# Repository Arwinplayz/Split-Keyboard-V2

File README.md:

# Split-Keyboard V2

I recently got my PCB from JLCPCB but I realised that I had accidentally inverted the holes for the hotswap sockets. This makes it physically impossible for me to actually assembly it properly. Learning from my failures, I decided to make a V2 which would not only fix the socket problem but also allow me to redo/refine some features. That is I want to add a LiPo battery and change the requirement of having both sides plugged in separately to the PC. I already have the parts to build the keyboard so the grant is only for the PCB (and possibly extra stuff such as LiPo battery, resistors, JST PH connectors, etc)

## Planning

I recently got my PCB from JLCPCB but I realised that I had accidentally inverted the holes for the hotswap sockets. This makes it physically impossible for me to actually assembly it properly. (Awkward placement + overlap with other components)

Learning from my failures, I decided to make a V2 which would not only fix the socket problem but also allow me to redo/refine some features. That is I want to add a LiPo battery and change the requirement of having both sides plugged in separately to the PC. I already have the parts to build the keyboard so the grant is only for the PCB (and possibly extra stuff such as LiPo battery, resistors, JST PH connectors, etc)

GOALS:

Fix hotswap socket orientation
Added better connectivity between the split keyboards (Master and Slave RP2040)
Add support for 1s 3.4V LiPo Battery

## Heavily Modified Schematic

So firstly, I realised that to use the master and slave approach, I needed a TRRS which connects the halves via UART. This meant that I needed a UARTTX, UARTRX but all my gpio pins were occupied. After some research I found that the nice!nano v2 was a good choice as it had the same Nordic chip. This allowed for bluetooth connection, a built in linear Li-Po charging circuit which helps avoid clutter. Furthermore, I added a 2 pin JST-PH connector for the Li-Po battery. There is also an RGB LED which will signal green for charged, yellow for 50$, red for low and blue for charging.

## Routed half the PCB

So I managed to route half the PCB now. There were many problems related to footprints as the Nice!Nano doesn't really have a goof publicly available one and so I had to design it myself. Also I added LED lights for every switch and ensured the hotswap sockets were orientated the right way.

## Finished Routing the PCB

So it took me a while to figure out how to mirror the left side. There was no easy way to do so I ended up flipping the edgecut and then redoing all the wiring. There is only 1 error on the ERC which is the left and right side aren't connected by this will get fixed with a TRRC cable.

## Gerber Files

I decided to get PCBA due to the keybaord requiring several LED and Diodes which all require a certain orientation to work properly. A few components require PCBA to be placed. I do have 1 or 2 components which I will hand solder myself to help reduce the costs. The PCB was too large for PCBA so I have to order each half of the PCB seperately.

## BOM

So since I already have most of the components such as rotary encoder, key switches, keycaps, etc, the BOM is prely for the parts I need for the PCB (the extra stuff that I didn't solder from JLC). So the total comes to about 227.98 USD. I really do not know how to make it cheaper as I've sourced everything from the cheapest sites I could find i.e aliexpress.

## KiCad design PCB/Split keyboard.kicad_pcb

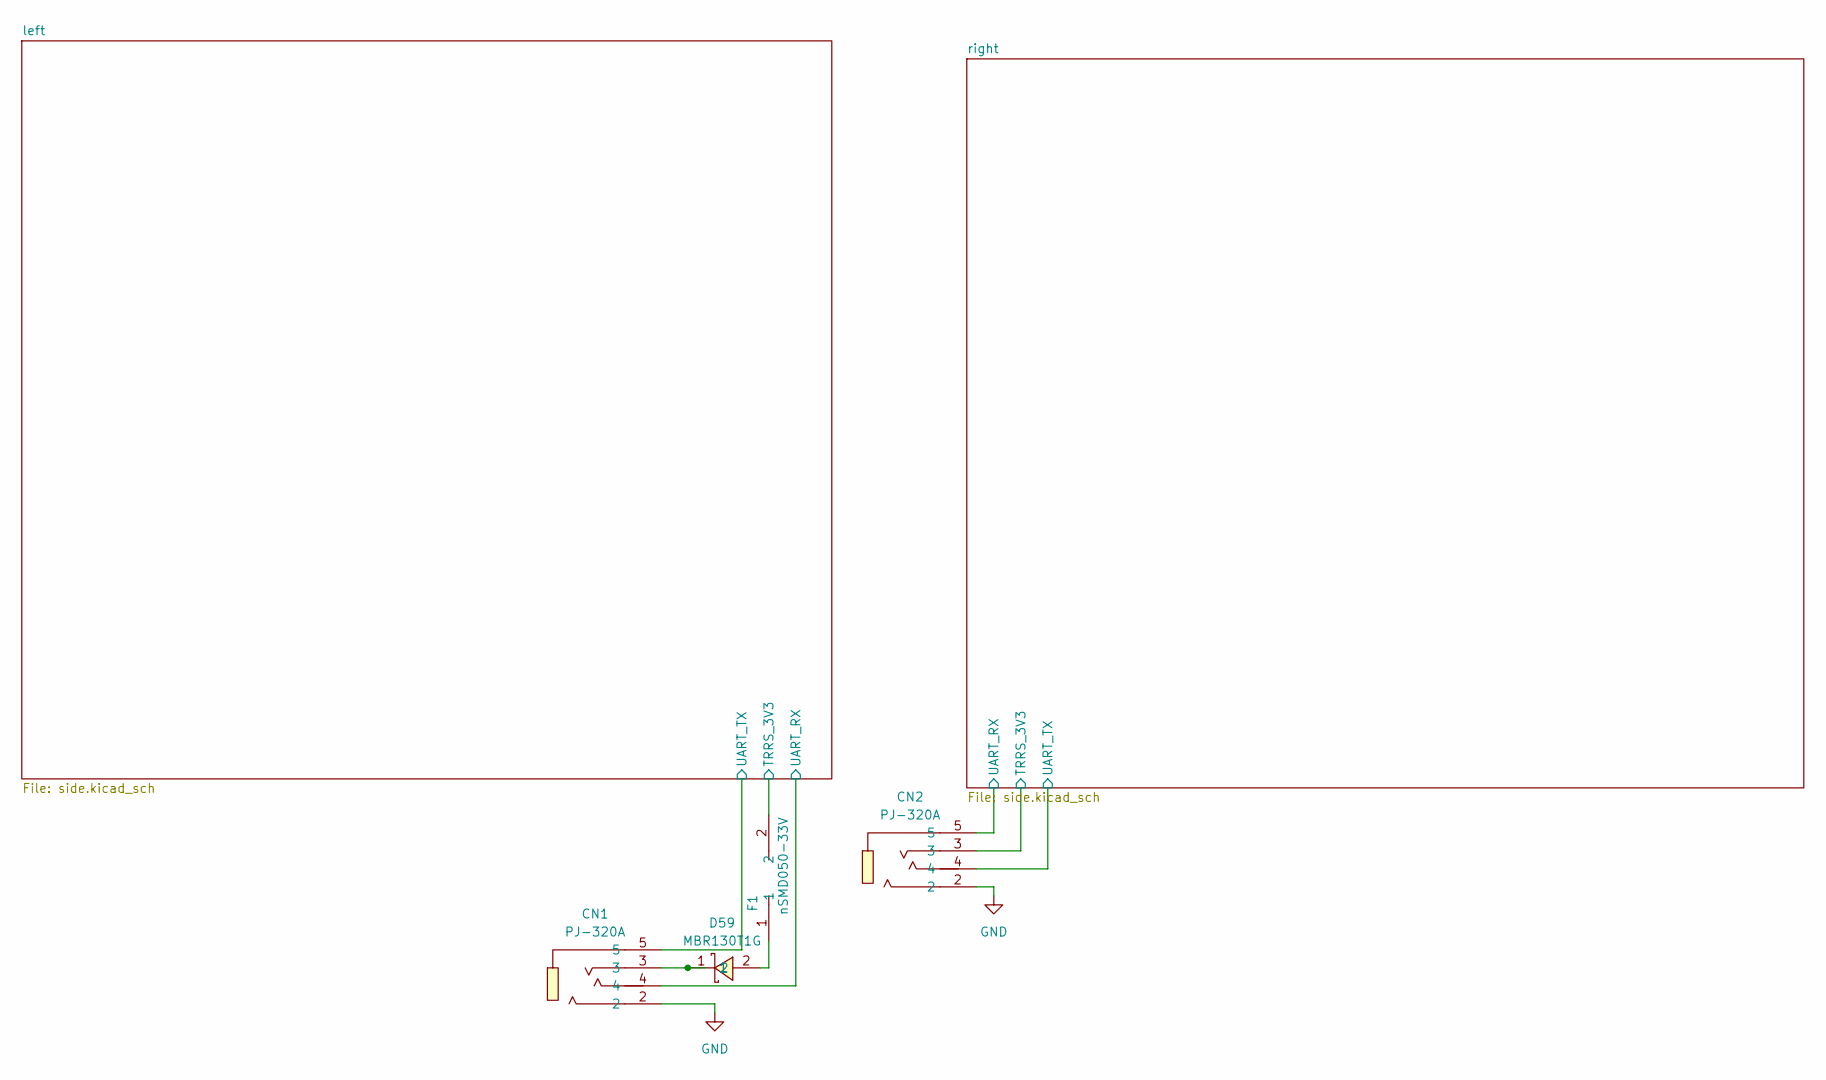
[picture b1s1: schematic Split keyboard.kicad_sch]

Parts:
CN1, CN2: PJ-320A; AUDIO-TH_XKB_PJ-320A; LCSC Part C2884926
D59: MBR130T1G; SOD-123_L2.8-W1.8-LS3.7-RD; LCSC Part C82461
F1: nSMD050-33V; F1206; LCSC Part C70077

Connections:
/left/UART_RX: CN1.4; also elsewhere on the board
/left/UART_TX: CN1.5; also elsewhere on the board
/left/VCC: F1.2; also elsewhere on the board
/right/UART_RX: CN2.5; also elsewhere on the board
/right/UART_TX: CN2.4; also elsewhere on the board
/right/VCC: CN2.3; also elsewhere on the board
GND: CN1.2, CN2.2; also elsewhere on the board
unnamed: CN1.3, D59.1
unnamed: D59.2, F1.1

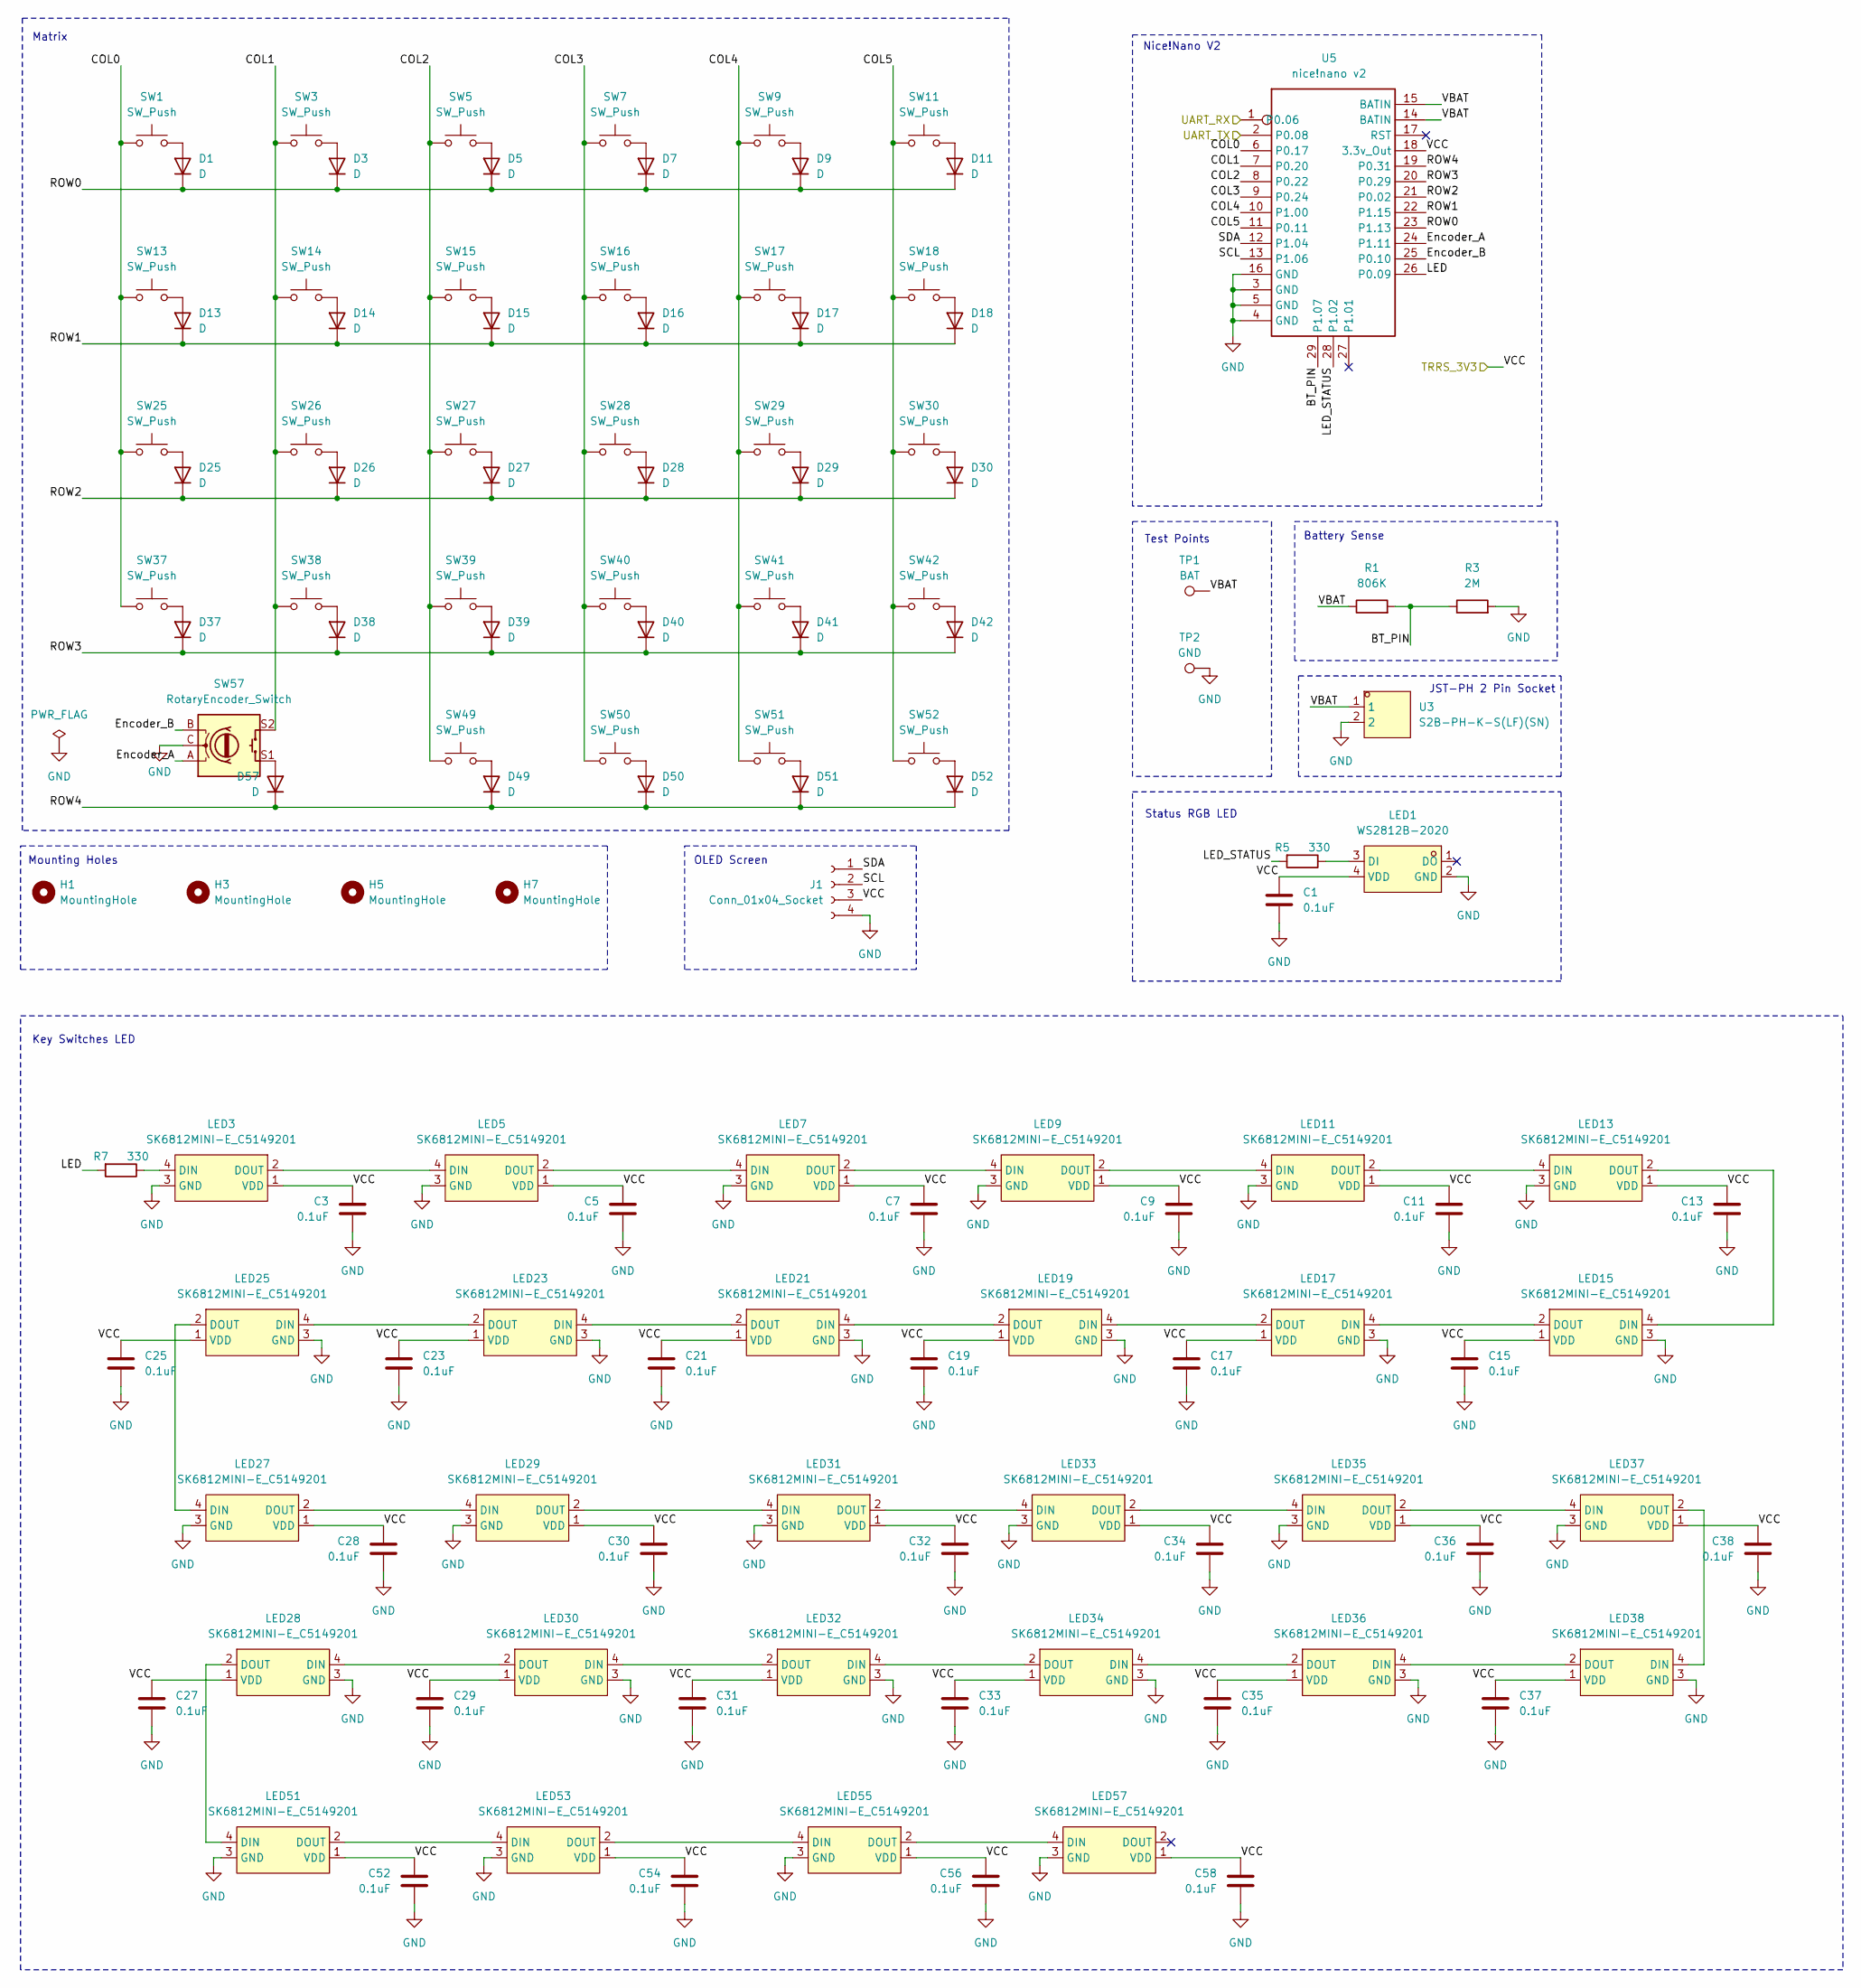
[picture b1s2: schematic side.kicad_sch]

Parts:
C1, C3, C5, C7, C9, C11, C13, C15, C17, C19, C21, C23, C25, C27, C28, C29, C30, C31, C32, C33, C34, C35, C36, C37, C38, C52, C54, C56, C58: 0.1uF; C_0603_1608Metric
D1, D3, D5, D7, D9, D11, D13, D14, D15, D16, D17, D18, D25, D26, D27, D28, D29, D30, D37, D38, D39, D40, D41, D42, D49, D50, D51, D52, D57: D; D_SOD-123
H1, H3, H5, H7: MountingHole; MountingHole_3.2mm_M3
J1: Conn_01x04_Socket; PinSocket_1x04_P2.54mm_Vertical
LED1: WS2812B-2020; LED-SMD_4P-L2.0-W2.0-TL_WS2812B-2020; LCSC Part C965555
LED3, LED5, LED7, LED9, LED11, LED13, LED15, LED17, LED19, LED21, LED23, LED25, LED27, LED28, LED29, LED30, LED31, LED32, LED33, LED34, LED35, LED36, LED37, LED38, LED51, LED53, LED55, LED57: SK6812MINI-E_C5149201; LED-SMD_L3.2-W2.8-LS5.9_SK6812MINI-E; LCSC Part C5149201
R1: 806K; R_0805_2012Metric
R3: 2M; R_0805_2012Metric
R5, R7: 330; R_0603_1608Metric
SW1, SW3, SW5, SW7, SW9, SW11, SW13, SW14, SW15, SW16, SW17, SW18, SW25, SW26, SW27, SW28, SW29, SW30, SW37, SW38, SW39, SW40, SW41, SW42, SW49, SW50, SW51, SW52: SW_Push; SW_choc_v1_HS_CPG135001S30_1u
SW57: RotaryEncoder_Switch; RotaryEncoder_Alps_EC11E-Switch_Vertical_H20mm
TP1: BAT; TestPoint_Pad_D2.0mm
TP2: GND; TestPoint_Pad_D2.0mm
U3: S2B-PH-K-S(LF)(SN); CONN-TH_S2B-PH-K-S-LF-SN; LCSC Part C173752
U5: nice!nano v2; NICE!NANO V2_2

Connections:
/left/BT_PIN: R1.2, R3.1, U5.29 (P1.07)
/left/COL0: SW1.1, SW13.1, SW25.1, SW37.1, U5.6 (P0.17)
/left/COL1: SW3.1, SW14.1, SW26.1, SW38.1, SW57.S2, U5.7 (P0.20)
/left/COL2: SW5.1, SW15.1, SW27.1, SW39.1, SW49.1, U5.8 (P0.22)
/left/COL3: SW7.1, SW16.1, SW28.1, SW40.1, SW50.1, U5.9 (P0.24)
/left/COL4: SW9.1, SW17.1, SW29.1, SW41.1, SW51.1, U5.10 (P1.00)
/left/COL5: SW11.1, SW18.1, SW30.1, SW42.1, SW52.1, U5.11 (P0.11)
/left/Encoder_A: SW57.A, U5.24 (P1.11)
/left/Encoder_B: SW57.B, U5.25 (P0.10)
/left/LED: R7.2, U5.26 (P0.09)
/left/LED_STATUS: R5.2, U5.28 (P1.02)
/left/ROW0: D1.1 (K), D3.1 (K), D5.1 (K), D7.1 (K), D9.1 (K), D11.1 (K), U5.23 (P1.13)
/left/ROW1: D13.1 (K), D14.1 (K), D15.1 (K), D16.1 (K), D17.1 (K), D18.1 (K), U5.22 (P1.15)
/left/ROW2: D25.1 (K), D26.1 (K), D27.1 (K), D28.1 (K), D29.1 (K), D30.1 (K), U5.21 (P0.02)
/left/ROW3: D37.1 (K), D38.1 (K), D39.1 (K), D40.1 (K), D41.1 (K), D42.1 (K), U5.20 (P0.29)
/left/ROW4: D49.1 (K), D50.1 (K), D51.1 (K), D52.1 (K), D57.1 (K), U5.19 (P0.31)
/left/SCL: J1.2, U5.13 (P1.06)
/left/SDA: J1.1, U5.12 (P1.04)
/left/UART_RX: U5.1 (P0.06); also elsewhere on the board
/left/UART_TX: U5.2 (P0.08); also elsewhere on the board
/left/VBAT: R1.1, TP1.1, U3.1, U5.14 (BATIN), U5.15 (BATIN)
/left/VCC: C1.1, C3.1, C5.1, C7.1, C9.1, C11.1, C13.1, C15.1, C17.1, C19.1, C21.1, C23.1, C25.1, C27.1, C28.1, C29.1, C30.1, C31.1, C32.1, C33.1, C34.1, C35.1, C36.1, C37.1, C38.1, C52.1, C54.1, C56.1, C58.1, J1.3, LED1.4 (VDD), LED3.1 (VDD), LED5.1 (VDD), LED7.1 (VDD), LED9.1 (VDD), LED11.1 (VDD), LED13.1 (VDD), LED15.1 (VDD), LED17.1 (VDD), LED19.1 (VDD), LED21.1 (VDD), LED23.1 (VDD), LED25.1 (VDD), LED27.1 (VDD), LED28.1 (VDD), LED29.1 (VDD), LED30.1 (VDD), LED31.1 (VDD), LED32.1 (VDD), LED33.1 (VDD), LED34.1 (VDD), LED35.1 (VDD), LED36.1 (VDD), LED37.1 (VDD), LED38.1 (VDD), LED51.1 (VDD), LED53.1 (VDD), LED55.1 (VDD), LED57.1 (VDD), U5.18 (3.3v_Out); also elsewhere on the board
GND: C1.2, C3.2, C5.2, C7.2, C9.2, C11.2, C13.2, C15.2, C17.2, C19.2, C21.2, C23.2, C25.2, C27.2, C28.2, C29.2, C30.2, C31.2, C32.2, C33.2, C34.2, C35.2, C36.2, C37.2, C38.2, C52.2, C54.2, C56.2, C58.2, J1.4, LED1.2 (GND), LED3.3 (GND), LED5.3 (GND), LED7.3 (GND), LED9.3 (GND), LED11.3 (GND), LED13.3 (GND), LED15.3 (GND), LED17.3 (GND), LED19.3 (GND), LED21.3 (GND), LED23.3 (GND), LED25.3 (GND), LED27.3 (GND), LED28.3 (GND), LED29.3 (GND), LED30.3 (GND), LED31.3 (GND), LED32.3 (GND), LED33.3 (GND), LED34.3 (GND), LED35.3 (GND), LED36.3 (GND), LED37.3 (GND), LED38.3 (GND), LED51.3 (GND), LED53.3 (GND), LED55.3 (GND), LED57.3 (GND), R3.2, SW57.C, TP2.1, U3.2, U5.3 (GND), U5.4 (GND), U5.5 (GND), U5.16 (GND); also elsewhere on the board
unnamed: D1.2 (A), SW1.2
unnamed: D3.2 (A), SW3.2
unnamed: D5.2 (A), SW5.2
unnamed: D7.2 (A), SW7.2
unnamed: D9.2 (A), SW9.2
unnamed: D11.2 (A), SW11.2
unnamed: D13.2 (A), SW13.2
unnamed: D14.2 (A), SW14.2
unnamed: D15.2 (A), SW15.2
unnamed: D16.2 (A), SW16.2
unnamed: D17.2 (A), SW17.2
unnamed: D18.2 (A), SW18.2
unnamed: D25.2 (A), SW25.2
unnamed: D26.2 (A), SW26.2
unnamed: D27.2 (A), SW27.2
unnamed: D28.2 (A), SW28.2
unnamed: D29.2 (A), SW29.2
unnamed: D30.2 (A), SW30.2
unnamed: D37.2 (A), SW37.2
unnamed: D38.2 (A), SW38.2
unnamed: D39.2 (A), SW39.2
unnamed: D40.2 (A), SW40.2
unnamed: D41.2 (A), SW41.2
unnamed: D42.2 (A), SW42.2
unnamed: D49.2 (A), SW49.2
unnamed: D50.2 (A), SW50.2
unnamed: D51.2 (A), SW51.2
unnamed: D52.2 (A), SW52.2
unnamed: D57.2 (A), SW57.S1
unnamed: LED1.3 (DI), R5.1
unnamed: LED3.4 (DIN), R7.1
unnamed: LED3.2 (DOUT), LED5.4 (DIN)
unnamed: LED5.2 (DOUT), LED7.4 (DIN)
unnamed: LED7.2 (DOUT), LED9.4 (DIN)
unnamed: LED9.2 (DOUT), LED11.4 (DIN)
unnamed: LED11.2 (DOUT), LED13.4 (DIN)
unnamed: LED13.2 (DOUT), LED15.4 (DIN)
unnamed: LED15.2 (DOUT), LED17.4 (DIN)
unnamed: LED17.2 (DOUT), LED19.4 (DIN)
unnamed: LED19.2 (DOUT), LED21.4 (DIN)
unnamed: LED21.2 (DOUT), LED23.4 (DIN)
unnamed: LED23.2 (DOUT), LED25.4 (DIN)
unnamed: LED25.2 (DOUT), LED27.4 (DIN)
unnamed: LED27.2 (DOUT), LED29.4 (DIN)
unnamed: LED28.4 (DIN), LED30.2 (DOUT)
unnamed: LED28.2 (DOUT), LED51.4 (DIN)
unnamed: LED29.2 (DOUT), LED31.4 (DIN)
unnamed: LED30.4 (DIN), LED32.2 (DOUT)
unnamed: LED31.2 (DOUT), LED33.4 (DIN)
unnamed: LED32.4 (DIN), LED34.2 (DOUT)
unnamed: LED33.2 (DOUT), LED35.4 (DIN)
unnamed: LED34.4 (DIN), LED36.2 (DOUT)
unnamed: LED35.2 (DOUT), LED37.4 (DIN)
unnamed: LED36.4 (DIN), LED38.2 (DOUT)
unnamed: LED37.2 (DOUT), LED38.4 (DIN)
unnamed: LED51.2 (DOUT), LED53.4 (DIN)
unnamed: LED53.2 (DOUT), LED55.4 (DIN)
unnamed: LED55.2 (DOUT), LED57.4 (DIN)

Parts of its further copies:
C2, C4, C6, C8, C10, C12, C14, C16, C18, C20, C22, C24, C26, C39, C40, C41, C42, C43, C44, C45, C46, C47, C48, C49, C50, C64, C66, C68, C70: 0.1uF; C_0603_1608Metric
D2, D4, D6, D8, D10, D12, D19, D20, D21, D22, D23, D24, D31, D32, D33, D34, D35, D36, D43, D44, D45, D46, D47, D48, D53, D54, D55, D56, D58: D; D_SOD-123
H2, H4, H6, H8: MountingHole; MountingHole_3.2mm_M3
J2: Conn_01x04_Socket; PinSocket_1x04_P2.54mm_Vertical
LED2: WS2812B-2020; LED-SMD_4P-L2.0-W2.0-TL_WS2812B-2020; LCSC Part C965555
LED4, LED6, LED8, LED10, LED12, LED14, LED16, LED18, LED20, LED22, LED24, LED26, LED39, LED40, LED41, LED42, LED43, LED44, LED45, LED46, LED47, LED48, LED49, LED50, LED63, LED65, LED67, LED69: SK6812MINI-E_C5149201; LED-SMD_L3.2-W2.8-LS5.9_SK6812MINI-E; LCSC Part C5149201
R2: 806K; R_0805_2012Metric
R4: 2M; R_0805_2012Metric
R6, R8: 330; R_0603_1608Metric
SW2, SW4, SW6, SW8, SW10, SW12, SW19, SW20, SW21, SW22, SW23, SW24, SW31, SW32, SW33, SW34, SW35, SW36, SW43, SW44, SW45, SW46, SW47, SW48, SW53, SW54, SW55, SW56: SW_Push; SW_choc_v1_HS_CPG135001S30_1u
SW58: RotaryEncoder_Switch; RotaryEncoder_Alps_EC11E-Switch_Vertical_H20mm
TP3: BAT; TestPoint_Pad_D2.0mm
TP4: GND; TestPoint_Pad_D2.0mm
U4: S2B-PH-K-S(LF)(SN); CONN-TH_S2B-PH-K-S-LF-SN; LCSC Part C173752
U6: nice!nano v2; NICE!NANO V2_2

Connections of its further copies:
/right/BT_PIN: R2.2, R4.1, U6.29 (P1.07)
/right/COL0: SW2.1, SW19.1, SW31.1, SW43.1, U6.6 (P0.17)
/right/COL1: SW4.1, SW20.1, SW32.1, SW44.1, SW58.S2, U6.7 (P0.20)
/right/COL2: SW6.1, SW21.1, SW33.1, SW45.1, SW53.1, U6.8 (P0.22)
/right/COL3: SW8.1, SW22.1, SW34.1, SW46.1, SW54.1, U6.9 (P0.24)
/right/COL4: SW10.1, SW23.1, SW35.1, SW47.1, SW55.1, U6.10 (P1.00)
/right/COL5: SW12.1, SW24.1, SW36.1, SW48.1, SW56.1, U6.11 (P0.11)
/right/Encoder_A: SW58.A, U6.24 (P1.11)
/right/Encoder_B: SW58.B, U6.25 (P0.10)
/right/LED: R8.2, U6.26 (P0.09)
/right/LED_STATUS: R6.2, U6.28 (P1.02)
/right/ROW0: D2.1 (K), D4.1 (K), D6.1 (K), D8.1 (K), D10.1 (K), D12.1 (K), U6.23 (P1.13)
/right/ROW1: D19.1 (K), D20.1 (K), D21.1 (K), D22.1 (K), D23.1 (K), D24.1 (K), U6.22 (P1.15)
/right/ROW2: D31.1 (K), D32.1 (K), D33.1 (K), D34.1 (K), D35.1 (K), D36.1 (K), U6.21 (P0.02)
/right/ROW3: D43.1 (K), D44.1 (K), D45.1 (K), D46.1 (K), D47.1 (K), D48.1 (K), U6.20 (P0.29)
/right/ROW4: D53.1 (K), D54.1 (K), D55.1 (K), D56.1 (K), D58.1 (K), U6.19 (P0.31)
/right/SCL: J2.2, U6.13 (P1.06)
/right/SDA: J2.1, U6.12 (P1.04)
/right/UART_RX: U6.1 (P0.06); also elsewhere on the board
/right/UART_TX: U6.2 (P0.08); also elsewhere on the board
/right/VBAT: R2.1, TP3.1, U4.1, U6.14 (BATIN), U6.15 (BATIN)
/right/VCC: C2.1, C4.1, C6.1, C8.1, C10.1, C12.1, C14.1, C16.1, C18.1, C20.1, C22.1, C24.1, C26.1, C39.1, C40.1, C41.1, C42.1, C43.1, C44.1, C45.1, C46.1, C47.1, C48.1, C49.1, C50.1, C64.1, C66.1, C68.1, C70.1, J2.3, LED2.4 (VDD), LED4.1 (VDD), LED6.1 (VDD), LED8.1 (VDD), LED10.1 (VDD), LED12.1 (VDD), LED14.1 (VDD), LED16.1 (VDD), LED18.1 (VDD), LED20.1 (VDD), LED22.1 (VDD), LED24.1 (VDD), LED26.1 (VDD), LED39.1 (VDD), LED40.1 (VDD), LED41.1 (VDD), LED42.1 (VDD), LED43.1 (VDD), LED44.1 (VDD), LED45.1 (VDD), LED46.1 (VDD), LED47.1 (VDD), LED48.1 (VDD), LED49.1 (VDD), LED50.1 (VDD), LED63.1 (VDD), LED65.1 (VDD), LED67.1 (VDD), LED69.1 (VDD), U6.18 (3.3v_Out); also elsewhere on the board
GND: C2.2, C4.2, C6.2, C8.2, C10.2, C12.2, C14.2, C16.2, C18.2, C20.2, C22.2, C24.2, C26.2, C39.2, C40.2, C41.2, C42.2, C43.2, C44.2, C45.2, C46.2, C47.2, C48.2, C49.2, C50.2, C64.2, C66.2, C68.2, C70.2, J2.4, LED2.2 (GND), LED4.3 (GND), LED6.3 (GND), LED8.3 (GND), LED10.3 (GND), LED12.3 (GND), LED14.3 (GND), LED16.3 (GND), LED18.3 (GND), LED20.3 (GND), LED22.3 (GND), LED24.3 (GND), LED26.3 (GND), LED39.3 (GND), LED40.3 (GND), LED41.3 (GND), LED42.3 (GND), LED43.3 (GND), LED44.3 (GND), LED45.3 (GND), LED46.3 (GND), LED47.3 (GND), LED48.3 (GND), LED49.3 (GND), LED50.3 (GND), LED63.3 (GND), LED65.3 (GND), LED67.3 (GND), LED69.3 (GND), R4.2, SW58.C, TP4.1, U4.2, U6.3 (GND), U6.4 (GND), U6.5 (GND), U6.16 (GND); also elsewhere on the board
unnamed: D2.2 (A), SW2.2
unnamed: D4.2 (A), SW4.2
unnamed: D6.2 (A), SW6.2
unnamed: D8.2 (A), SW8.2
unnamed: D10.2 (A), SW10.2
unnamed: D12.2 (A), SW12.2
unnamed: D19.2 (A), SW19.2
unnamed: D20.2 (A), SW20.2
unnamed: D21.2 (A), SW21.2
unnamed: D22.2 (A), SW22.2
unnamed: D23.2 (A), SW23.2
unnamed: D24.2 (A), SW24.2
unnamed: D31.2 (A), SW31.2
unnamed: D32.2 (A), SW32.2
unnamed: D33.2 (A), SW33.2
unnamed: D34.2 (A), SW34.2
unnamed: D35.2 (A), SW35.2
unnamed: D36.2 (A), SW36.2
unnamed: D43.2 (A), SW43.2
unnamed: D44.2 (A), SW44.2
unnamed: D45.2 (A), SW45.2
unnamed: D46.2 (A), SW46.2
unnamed: D47.2 (A), SW47.2
unnamed: D48.2 (A), SW48.2
unnamed: D53.2 (A), SW53.2
unnamed: D54.2 (A), SW54.2
unnamed: D55.2 (A), SW55.2
unnamed: D56.2 (A), SW56.2
unnamed: D58.2 (A), SW58.S1
unnamed: LED2.3 (DI), R6.1
unnamed: LED4.4 (DIN), R8.1
unnamed: LED4.2 (DOUT), LED6.4 (DIN)
unnamed: LED6.2 (DOUT), LED8.4 (DIN)
unnamed: LED8.2 (DOUT), LED10.4 (DIN)
unnamed: LED10.2 (DOUT), LED12.4 (DIN)
unnamed: LED12.2 (DOUT), LED14.4 (DIN)
unnamed: LED14.2 (DOUT), LED16.4 (DIN)
unnamed: LED16.2 (DOUT), LED18.4 (DIN)
unnamed: LED18.2 (DOUT), LED20.4 (DIN)
unnamed: LED20.2 (DOUT), LED22.4 (DIN)
unnamed: LED22.2 (DOUT), LED24.4 (DIN)
unnamed: LED24.2 (DOUT), LED26.4 (DIN)
unnamed: LED26.2 (DOUT), LED39.4 (DIN)
unnamed: LED39.2 (DOUT), LED41.4 (DIN)
unnamed: LED40.4 (DIN), LED42.2 (DOUT)
unnamed: LED40.2 (DOUT), LED63.4 (DIN)
unnamed: LED41.2 (DOUT), LED43.4 (DIN)
unnamed: LED42.4 (DIN), LED44.2 (DOUT)
unnamed: LED43.2 (DOUT), LED45.4 (DIN)
unnamed: LED44.4 (DIN), LED46.2 (DOUT)
unnamed: LED45.2 (DOUT), LED47.4 (DIN)
unnamed: LED46.4 (DIN), LED48.2 (DOUT)
unnamed: LED47.2 (DOUT), LED49.4 (DIN)
unnamed: LED48.4 (DIN), LED50.2 (DOUT)
unnamed: LED49.2 (DOUT), LED50.4 (DIN)
unnamed: LED63.2 (DOUT), LED65.4 (DIN)
unnamed: LED65.2 (DOUT), LED67.4 (DIN)
unnamed: LED67.2 (DOUT), LED69.4 (DIN)

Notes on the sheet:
OLED Screen
Nice!Nano V2
Battery Sense
Mounting Holes
Key Switches LED
Status RGB LED
Matrix
JST-PH 2 Pin Socket
Test Points

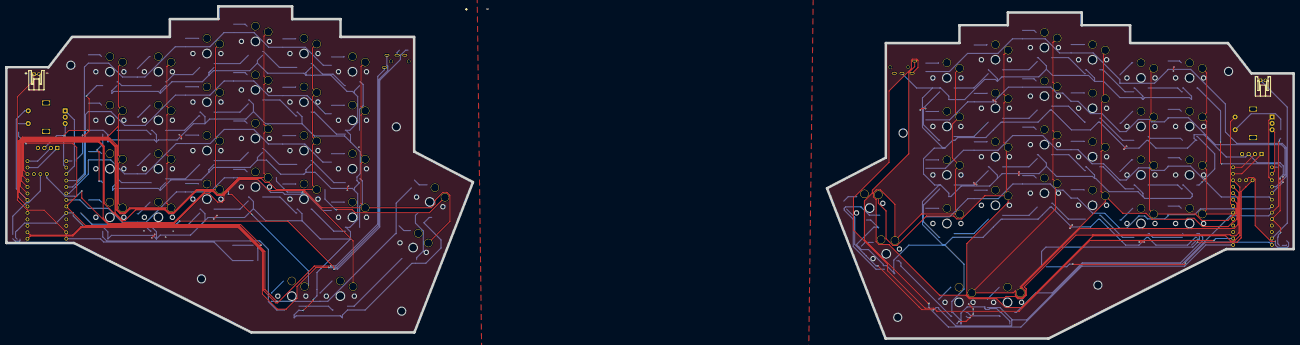
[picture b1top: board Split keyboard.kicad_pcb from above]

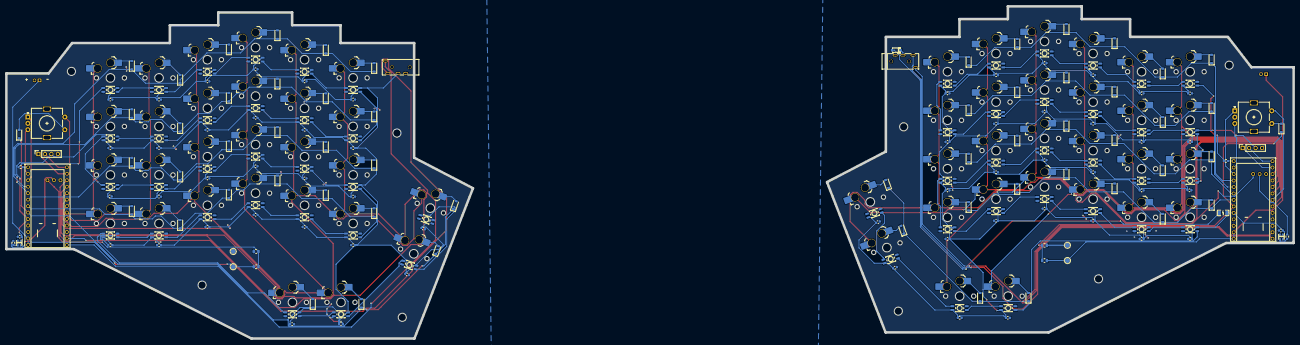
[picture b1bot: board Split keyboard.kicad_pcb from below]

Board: 2 copper layers, 505.4 x 130.4 mm, 262 parts (256 on the bottom side), 163 nets.

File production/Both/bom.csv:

Designator,Footprint,Quantity,Value,LCSC Part #
"C1, C10, C11, C12, C13, C14, C15, C16, C17, C18, C19, C2, C20, C21, C22, C23, C24, C25, C26, C27, C28, C29, C3, C30, C31, C32, C33, C34, C35, C36, C37, C38, C39, C4, C40, C41, C42, C43, C44, C45, C46, C47, C48, C49, C5, C50, C52, C54, C56, C58, C6, C64, C66, C68, C7, C70, C8, C9",0603,58,0.1uF,
"CN1, CN2",AUDIO-TH_XKB_PJ-320A,2,PJ-320A,C2884926
"D1, D10, D11, D12, D13, D14, D15, D16, D17, D18, D19, D2, D20, D21, D22, D23, D24, D25, D26, D27, D28, D29, D3, D30, D31, D32, D33, D34, D35, D36, D37, D38, D39, D4, D40, D41, D42, D43, D44, D45, D46, D47, D48, D49, D5, D50, D51, D52, D53, D54, D55, D56, D57, D58, D6, D7, D8, D9",D_SOD-123,58,D,
D59,SOD-123_L2.8-W1.8-LS3.7-RD,1,MBR130T1G,C82461
F1,F1206,1,nSMD050-33V,C70077
"J1, J2",PinSocket_1x04_P2.54mm_Vertical,2,Conn_01x04_Socket,
"LED1, LED2",LED-SMD_4P-L2.0-W2.0-TL_WS2812B-2020,2,WS2812B-2020,C965555
"LED10, LED11, LED12, LED13, LED14, LED15, LED16, LED17, LED18, LED19, LED20, LED21, LED22, LED23, LED24, LED25, LED26, LED27, LED28, LED29, LED3, LED30, LED31, LED32, LED33, LED34, LED35, LED36, LED37, LED38, LED39, LED4, LED40, LED41, LED42, LED43, LED44, LED45, LED46, LED47, LED48, LED49, LED5, LED50, LED51, LED53, LED55, LED57, LED6, LED63, LED65, LED67, LED69, LED7, LED8, LED9",LED-SMD_L3.2-W2.8-LS5.9_SK6812MINI-E,56,SK6812MINI-E_C5149201,C5149201
"R1, R2",0805,2,806K,
"R3, R4",0805,2,2M,
"R5, R6, R7, R8",0603,4,330,
"SW1, SW10, SW11, SW12, SW13, SW14, SW15, SW16, SW17, SW18, SW19, SW2, SW20, SW21, SW22, SW23, SW24, SW25, SW26, SW27, SW28, SW29, SW3, SW30, SW31, SW32, SW33, SW34, SW35, SW36, SW37, SW38, SW39, SW4, SW40, SW41, SW42, SW43, SW44, SW45, SW46, SW47, SW48, SW49, SW5, SW50, SW51, SW52, SW53, SW54, SW55, SW56, SW6, SW7, SW8, SW9",SW_choc_v1_HS_CPG135001S30_1u,56,SW_Push,
"SW57, SW58",RotaryEncoder_Alps_EC11E-Switch_Vertical_H20mm,2,RotaryEncoder_Switch,
"TP1, TP3",TestPoint_Pad_D2.0mm,2,BAT,
"TP2, TP4",TestPoint_Pad_D2.0mm,2,GND,
"U3, U4",CONN-TH_S2B-PH-K-S-LF-SN,2,S2B-PH-K-S(LF)(SN),C173752
"U5, U6",NICE!NANO V2_2,2,nice!nano v2,

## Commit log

2026-01-10 added local files
2026-03-23 added BLOG
